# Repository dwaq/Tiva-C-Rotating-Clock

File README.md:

# Tiva-C-Rotating-Clock

My sister bought me the [SainSmart Rotating LED Electronic Digital Clock DIY Kit](https://www.sainsmart.com/products/rotating-led-electronic-digital-clock-diy-kit) as a birthday present and after assembling it, it just didn't work. After debugging it for a bit, I realized that Atmel AT89S52 microcontroller wasn't doing anything. I tried to read the memory out, but it was either blank, damaged, or I was locked out. So at this point, I did what any sane engineer would do and spent countless hours designing a PCB adapter board and writing code for another microcontroller so I could use my $10.99 gift.

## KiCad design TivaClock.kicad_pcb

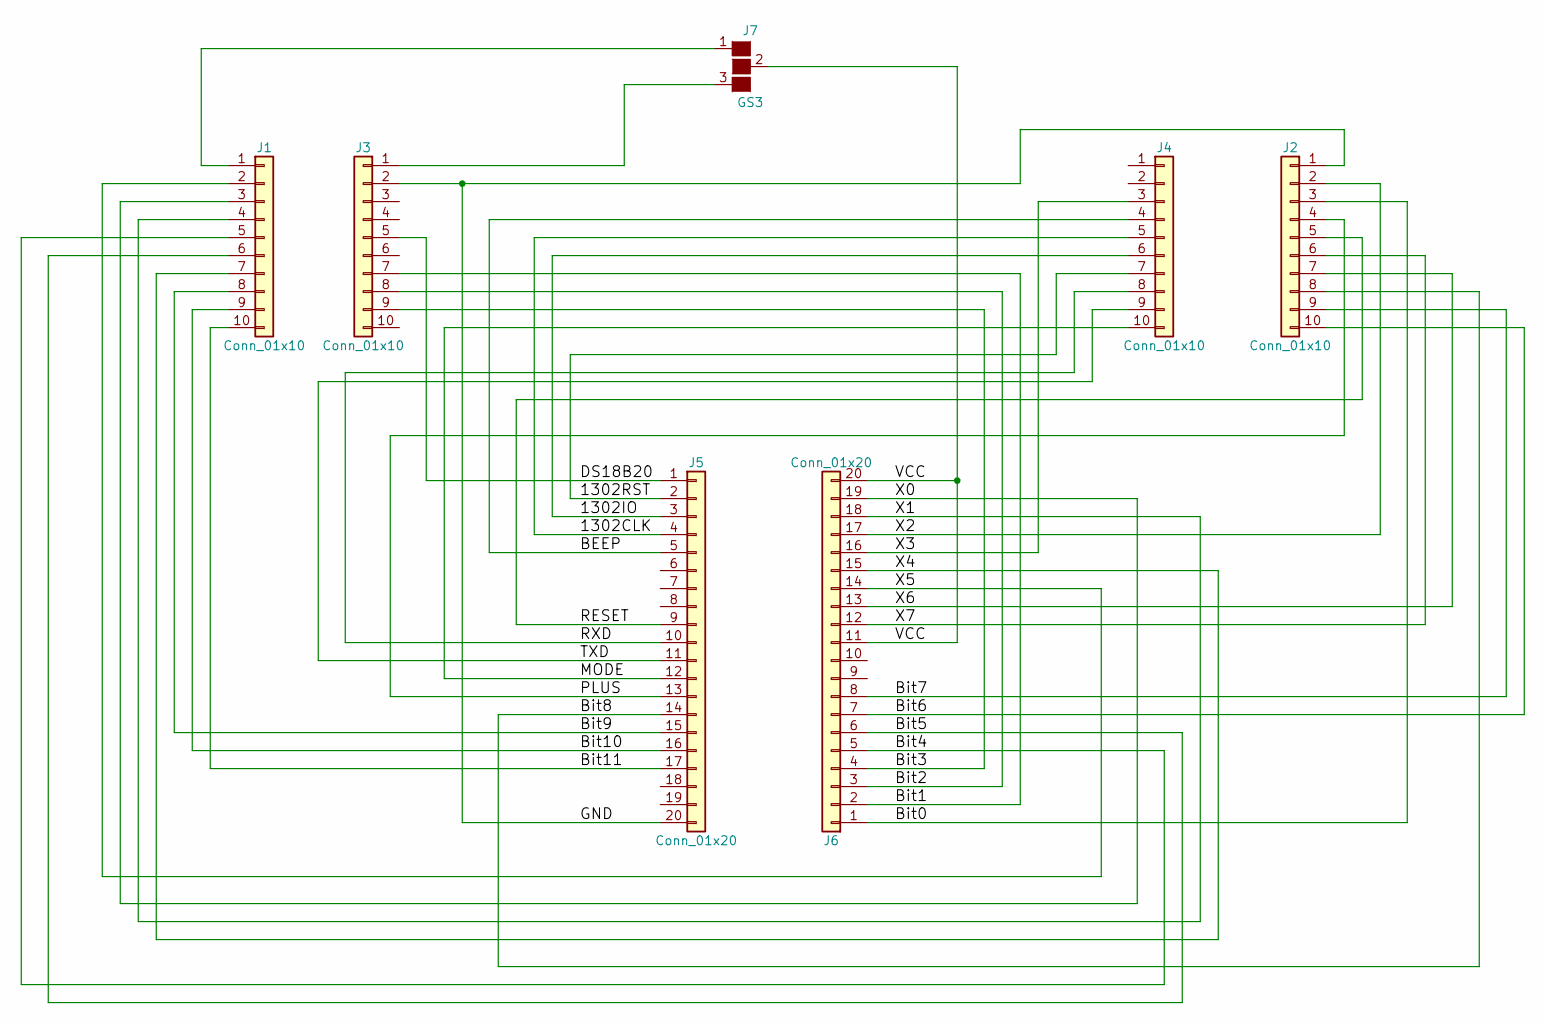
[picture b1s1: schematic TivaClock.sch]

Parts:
J1, J2, J3, J4: Conn_01x10; Pin_Header_Straight_1x10_Pitch2.54mm
J5, J6: Conn_01x20; Pin_Header_Straight_1x20_Pitch2.54mm
J7: GS3

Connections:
/1302CLK: J4.5, J5.4
/1302IO: J4.6, J5.3
/1302RST: J4.7, J5.2
/BEEP: J4.4, J5.5
/Bit0: J2.3, J6.1
/Bit1: J3.7, J6.2
/Bit2: J3.8, J6.3
/Bit3: J3.9, J6.4
/Bit4: J1.5, J6.5
/Bit5: J1.6, J6.6
/Bit6: J2.10, J6.7
/Bit7: J2.9, J6.8
/Bit8: J2.8, J5.14
/Bit9: J1.8, J5.15
/Bit10: J1.9, J5.16
/Bit11: J1.10, J5.17
/DS18B20: J3.5, J5.1
/GND: J2.1, J3.2, J5.20
/MODE: J4.10, J5.12
/PLUS: J2.4, J5.13
/RESET: J2.5, J5.9
/RXD: J4.8, J5.10
/TXD: J4.9, J5.11
/VCC: J6.11, J6.20, J7.2 (G2)
/X0: J1.3, J6.19
/X1: J1.4, J6.18
/X2: J2.2, J6.17
/X3: J4.3, J6.16
/X4: J1.7, J6.15
/X5: J1.2, J6.14
/X6: J2.7, J6.13
/X7: J2.6, J6.12
unnamed: J1.1, J7.1 (G1)
unnamed: J3.1, J7.3 (G3)

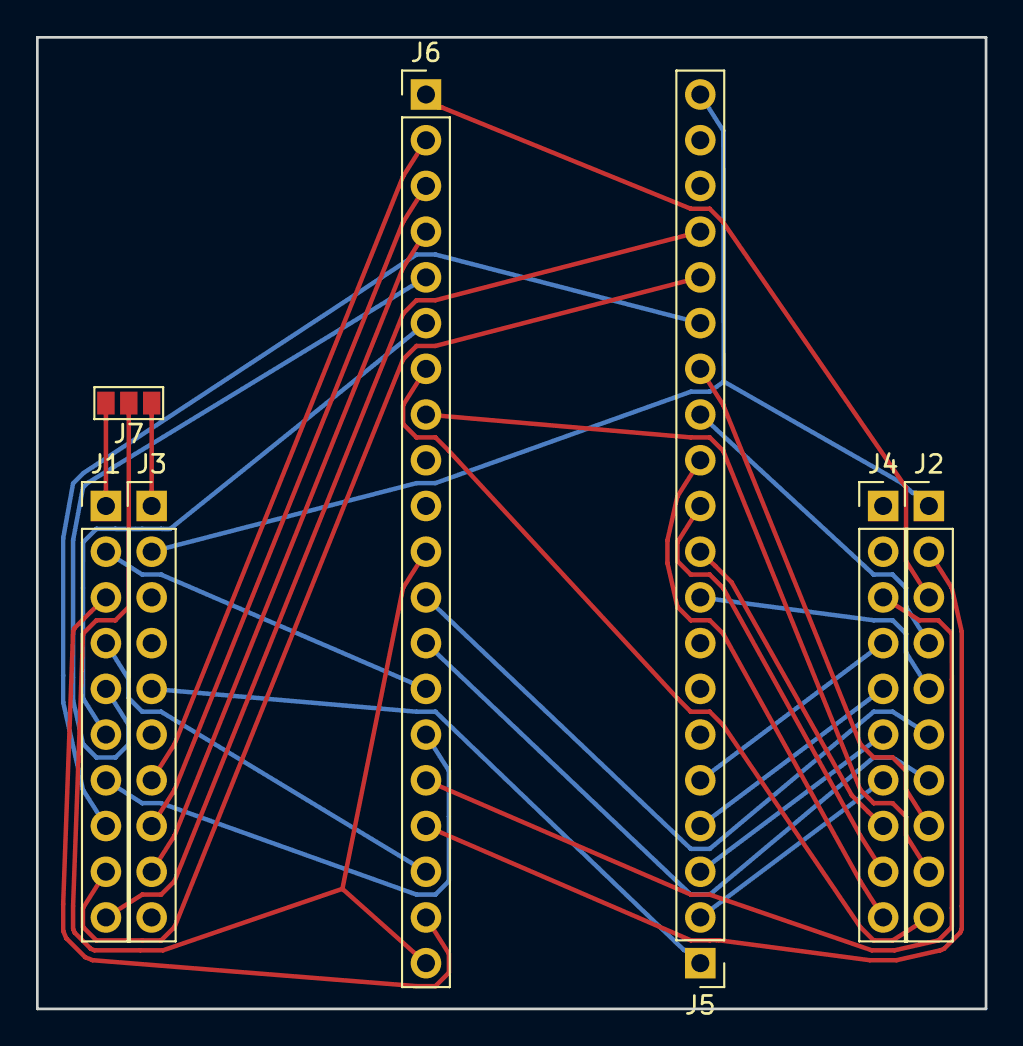
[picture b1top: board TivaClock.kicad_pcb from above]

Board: 2 copper layers, 52.7 x 54.0 mm, 7 parts (0 on the bottom side), 34 nets.

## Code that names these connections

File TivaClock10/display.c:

#include "display.h"
#include "delay.h"

#include <stdint.h>
#include <stdbool.h>
#include "inc/hw_memmap.h"
#include "driverlib/gpio.h"
#include "driverlib/sysctl.h"

#define BLANK 0x10

// set all LED pins to outputs
void displaySetup(void) {
    // Enable the GPIO ports
    SysCtlPeripheralEnable(SYSCTL_PERIPH_GPIOA);
    SysCtlPeripheralEnable(SYSCTL_PERIPH_GPIOB);
    SysCtlPeripheralEnable(SYSCTL_PERIPH_GPIOE);
    SysCtlPeripheralEnable(SYSCTL_PERIPH_GPIOF);

    // Check if the peripheral access is enabled
    while (!SysCtlPeripheralReady(SYSCTL_PERIPH_GPIOA)) {}
    while (!SysCtlPeripheralReady(SYSCTL_PERIPH_GPIOB)) {}
    while (!SysCtlPeripheralReady(SYSCTL_PERIPH_GPIOE)) {}
    while (!SysCtlPeripheralReady(SYSCTL_PERIPH_GPIOF)) {}

    // Set the GPIOs as digital outputs
    GPIOPinTypeGPIOOutput(GPIO_PORTE_BASE, GPIO_PIN_0); // X0
    GPIOPinTypeGPIOOutput(GPIO_PORTE_BASE, GPIO_PIN_1); // X1
    GPIOPinTypeGPIOOutput(GPIO_PORTE_BASE, GPIO_PIN_2); // X2
    GPIOPinTypeGPIOOutput(GPIO_PORTE_BASE, GPIO_PIN_3); // X3
    GPIOPinTypeGPIOOutput(GPIO_PORTE_BASE, GPIO_PIN_4); // X4
    GPIOPinTypeGPIOOutput(GPIO_PORTE_BASE, GPIO_PIN_5); // X5

    GPIOPinTypeGPIOOutput(GPIO_PORTA_BASE, GPIO_PIN_2); // X6
    GPIOPinTypeGPIOOutput(GPIO_PORTA_BASE, GPIO_PIN_3); // X7
    GPIOPinTypeGPIOOutput(GPIO_PORTA_BASE, GPIO_PIN_4); // X8
    GPIOPinTypeGPIOOutput(GPIO_PORTA_BASE, GPIO_PIN_5); // X9
    GPIOPinTypeGPIOOutput(GPIO_PORTA_BASE, GPIO_PIN_6); // X10
    GPIOPinTypeGPIOOutput(GPIO_PORTA_BASE, GPIO_PIN_7); // X11

    GPIOPinTypeGPIOOutput(GPIO_PORTB_BASE, GPIO_PIN_0); // Bit0
    GPIOPinTypeGPIOOutput(GPIO_PORTB_BASE, GPIO_PIN_1); // Bit1
    GPIOPinTypeGPIOOutput(GPIO_PORTB_BASE, GPIO_PIN_2); // Bit2
    GPIOPinTypeGPIOOutput(GPIO_PORTB_BASE, GPIO_PIN_3); // Bit3
    GPIOPinTypeGPIOOutput(GPIO_PORTB_BASE, GPIO_PIN_4); // Bit4
    GPIOPinTypeGPIOOutput(GPIO_PORTB_BASE, GPIO_PIN_5); // Bit5
    GPIOPinTypeGPIOOutput(GPIO_PORTB_BASE, GPIO_PIN_6); // Bit6
    GPIOPinTypeGPIOOutput(GPIO_PORTB_BASE, GPIO_PIN_7); // Bit7
}

// cycle through and display each digit
// dp is for decimal point: 0 for off; 1 for on
void displayDigits(int dig1, int dig2, int dp, int dig3, int dig4) {
    // don't display anything on dig1 if it's '0'
    if(dig1 == 0)
        setDigit(1, BLANK);
    else
        setDigit(1, dig1);

    setDigit(2, dig2);
    setDigit(3, dig3);
    setDigit(4, dig4);
    if (dp) {
        // display decimal point (special parameter)
        decimalpoint();
    }
}

// display a number on the selected digit 1, 2, 3, or 4
void setDigit(int digit, int number) {
    // turn on specific digit
    switch (digit) {
    case 1:
        setSegment(number);
        GPIOPinWrite(GPIO_PORTA_BASE, GPIO_PIN_4, 0); // Bit 8
        Delay(DISPLAY_DELAY);
        GPIOPinWrite(GPIO_PORTA_BASE, GPIO_PIN_4, GPIO_PIN_4); // Bit 8
        break;
    case 2:
        setSegment(number);
        GPIOPinWrite(GPIO_PORTA_BASE, GPIO_PIN_5, 0); // Bit 9
        Delay(DISPLAY_DELAY);
        GPIOPinWrite(GPIO_PORTA_BASE, GPIO_PIN_5, GPIO_PIN_5); // Bit 9
        break;
    case 3:
        setSegment(number);
        GPIOPinWrite(GPIO_PORTA_BASE, GPIO_PIN_6, 0); // Bit 10
        Delay(DISPLAY_DELAY);
        GPIOPinWrite(GPIO_PORTA_BASE, GPIO_PIN_6, GPIO_PIN_6); // Bit 10
        break;
    case 4:
        setSegment(number);
        GPIOPinWrite(GPIO_PORTA_BASE, GPIO_PIN_7, 0); // Bit 11
        Delay(DISPLAY_DELAY);
        GPIOPinWrite(GPIO_PORTA_BASE, GPIO_PIN_7, GPIO_PIN_7); // Bit 11
        break;
        //default:
        // bad - should't be here
    }
}

// display a number or symbol using the 7 segments
// number can be between 0-9 or settings screen uses A-F
void setSegment(int number) {
    // first, reset all segments

    // then set the corresponding segments
    switch (number) {
    case 0:
        // A B C D E F
        GPIOPinWrite(GPIO_PORTB_BASE, 0xFF, 0b11000000);
        break;
    case 1:
        // B C
        GPIOPinWrite(GPIO_PORTB_BASE, 0xFF, 0b11111001);
        break;
    case 2:
        // A B D E G
        GPIOPinWrite(GPIO_PORTB_BASE, 0xFF, 0b10100100);
        break;
    case 3:
        // A B C D G
        GPIOPinWrite(GPIO_PORTB_BASE, 0xFF, 0b10110000);
        break;
    case 4:
        // B C F G
        GPIOPinWrite(GPIO_PORTB_BASE, 0xFF, 0b10011001);
        break;
    case 5:
        // A C D F G
        GPIOPinWrite(GPIO_PORTB_BASE, 0xFF, 0b10010010);
        break;
    case 6:
        // A C D E F G
        GPIOPinWrite(GPIO_PORTB_BASE, 0xFF, 0b10000010);
        break;
    case 7:
        // A B C
        GPIOPinWrite(GPIO_PORTB_BASE, 0xFF, 0b11111000);
        break;
    case 8:
        // A B C D E F G
        GPIOPinWrite(GPIO_PORTB_BASE, 0xFF, 0b10000000);
        break;
    case 9:
        // A B C D F G
        GPIOPinWrite(GPIO_PORTB_BASE, 0xFF, 0b10010000);
        break;
    case 0xA:
        // A B C E F G
        GPIOPinWrite(GPIO_PORTB_BASE, 0xFF, 0b10001000);
        break;
    case 0xB:
        // A B C D E F G
        GPIOPinWrite(GPIO_PORTB_BASE, 0xFF, 0b10000000);
        break;
    case 0xC:
        // A D E F
        GPIOPinWrite(GPIO_PORTB_BASE, 0xFF, 0b11000110);
        break;
    case 0xD:
        // A B C D E F
        GPIOPinWrite(GPIO_PORTB_BASE, 0xFF, 0b11000000);
        break;
    case 0xE:
        // A D E F G
        GPIOPinWrite(GPIO_PORTB_BASE, 0xFF, 0b10000110);
        break;
    case 0xF:
        // A E F G
        GPIOPinWrite(GPIO_PORTB_BASE, 0xFF, 0b10001110);
        break;
    default:
        // case BLANK falls through here
        // turns off all of the segments
        GPIOPinWrite(GPIO_PORTB_BASE, 0xFF, 0b11111111);
        break;
    };
}

void decimalpoint(void) {
    GPIOPinWrite(GPIO_PORTA_BASE, GPIO_PIN_5, 0); // Bit 9
    GPIOPinWrite(GPIO_PORTB_BASE, 0xFF, 0b01111111);
    Delay(TIMER_DELAY);
    GPIOPinWrite(GPIO_PORTA_BASE, GPIO_PIN_5, GPIO_PIN_5); // Bit 9
}

void displaySeconds(int digit) {
    if (digit > 56) {
        GPIOPinWrite(GPIO_PORTB_BASE, 0xFF, (~0 << (digit - 56)));
        GPIOPinWrite(GPIO_PORTA_BASE, GPIO_PIN_3, 0); // Bit 7
        Delay(TIMER_DELAY);
        GPIOPinWrite(GPIO_PORTA_BASE, GPIO_PIN_3, GPIO_PIN_3); // Bit 7
        digit = 56;
    }
    if (digit > 48) {
        GPIOPinWrite(GPIO_PORTB_BASE, 0xFF, (~0 << (digit - 48)));
        GPIOPinWrite(GPIO_PORTA_BASE, GPIO_PIN_2, 0); // Bit 6
        Delay(TIMER_DELAY);
        GPIOPinWrite(GPIO_PORTA_BASE, GPIO_PIN_2, GPIO_PIN_2); // Bit 6
        digit = 48;
    }
    if (digit > 40) {
        GPIOPinWrite(GPIO_PORTB_BASE, 0xFF, (~0 << (digit - 40)));
        GPIOPinWrite(GPIO_PORTE_BASE, GPIO_PIN_5, 0); // Bit 5
        Delay(TIMER_DELAY);
        GPIOPinWrite(GPIO_PORTE_BASE, GPIO_PIN_5, GPIO_PIN_5); // Bit 5
        digit = 40;
    }
    if (digit > 32) {
        GPIOPinWrite(GPIO_PORTB_BASE, 0xFF, (~0 << (digit - 32)));
        GPIOPinWrite(GPIO_PORTE_BASE, GPIO_PIN_4, 0); // Bit 4
        Delay(TIMER_DELAY);
        GPIOPinWrite(GPIO_PORTE_BASE, GPIO_PIN_4, GPIO_PIN_4); // Bit 4
        digit = 32;
    }
    if (digit > 24) {
        GPIOPinWrite(GPIO_PORTB_BASE, 0xFF, (~0 << (digit - 24)));
        GPIOPinWrite(GPIO_PORTE_BASE, GPIO_PIN_3, 0); // Bit 3
        Delay(TIMER_DELAY);
        GPIOPinWrite(GPIO_PORTE_BASE, GPIO_PIN_3, GPIO_PIN_3); // Bit 3
        digit = 24;
    }
    if (digit > 16) {
        GPIOPinWrite(GPIO_PORTB_BASE, 0xFF, (~0 << (digit - 16)));
        GPIOPinWrite(GPIO_PORTE_BASE, GPIO_PIN_2, 0); // Bit 2
        Delay(TIMER_DELAY);
        GPIOPinWrite(GPIO_PORTE_BASE, GPIO_PIN_2, GPIO_PIN_2); // Bit 2
        digit = 16;
    }
    if (digit > 8) {
        GPIOPinWrite(GPIO_PORTB_BASE, 0xFF, (~0 << (digit - 8)));
        GPIOPinWrite(GPIO_PORTE_BASE, GPIO_PIN_1, 0); // Bit 1
        Delay(TIMER_DELAY);
        GPIOPinWrite(GPIO_PORTE_BASE, GPIO_PIN_1, GPIO_PIN_1); // Bit 1
        digit = 8;
    }
    if (digit >= 0) {
        GPIOPinWrite(GPIO_PORTB_BASE, 0xFF, (~0 << (digit - 0)));
        GPIOPinWrite(GPIO_PORTE_BASE, GPIO_PIN_0, 0); // Bit 0
        Delay(TIMER_DELAY);
        GPIOPinWrite(GPIO_PORTE_BASE, GPIO_PIN_0, GPIO_PIN_0); // Bit 0
    }
}

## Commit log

2018-01-14 added headers and Clock pin names
2018-01-23 add some more stuff
2018-01-24 connect important peripherals
2018-01-24 connected LED wires
2018-01-24 connected all remaining pins
    except power
2018-01-24 annotate clock headers
2018-01-24 generate netlist
2018-01-24 place launchpad headers where they belong
2018-01-24 added footprints and locations
2018-01-26 ignore any temp kicad file
2018-01-26 move clock micro to desired location
2018-01-26 orientate it corectly?
2018-01-26 export design as specctra file
2018-01-26 autorouted
2018-01-26 add jumper to connect 3.3V or 5V to board VCC
2018-01-26 put solder jumper on PCB
2018-01-26 reroute with solder jumper
2018-01-26 save n exit
2018-01-26 add gerber files
2018-02-09 Add some no connects to schematic to make ERC happy
2018-02-09 add images of schematic and layout
2018-02-10 Add pin names to launchpad headers
2018-02-11 add code that drives all LEDs
2018-02-11 Add all include files for chip
2018-02-11 Add all driverlib files for chip
2018-02-11 Add all CCS files
2018-02-11 reformat code
2018-02-11 move auxillary functions to new files
2020-08-29 Duplicate project for CCS10
2020-08-29 include main.c
2020-08-29 exclude other CSS files
2020-08-29 Set up SysTick for 1 second interrupt
2020-08-29 Keep all previous seconds lit when increasing
2020-08-29 get started on RTC library & set up pins
2020-08-29 Change RTC I/O pin & get comms working
2020-08-29 add some comments
2020-08-29 display the seconds
2020-08-29 format hours mins & secs and display
2020-08-29 don't display anything on 10's hour if it's 0
2020-08-29 combine seconds and display on LED ring
2020-08-29 flash the decimal point with every second
2020-09-13 Convert bit-banged pins to I2C3 (PD0/PD1)
2020-09-13 Reduce every delay for RTC
2020-09-13 get data from RTC once a second using systick
    Causes a small delay which affects the lighting of the display
2020-09-13 Explain SysTick method
2020-09-13 Start explaination
2020-09-14 Move KiCad files into PCB directory
2020-09-14 add one to make 0 display at the top-most position
2020-09-14 sort out the git files
2020-09-14 Switch order of LED pin writes to illuminate them better
2020-09-14 Switch order of Display pin writes to illuminate them better
2020-09-14 Always keep decimal point on
